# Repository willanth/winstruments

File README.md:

# winstruments
Interface and control PCB for interfacing with professional environmental monitoring instruments

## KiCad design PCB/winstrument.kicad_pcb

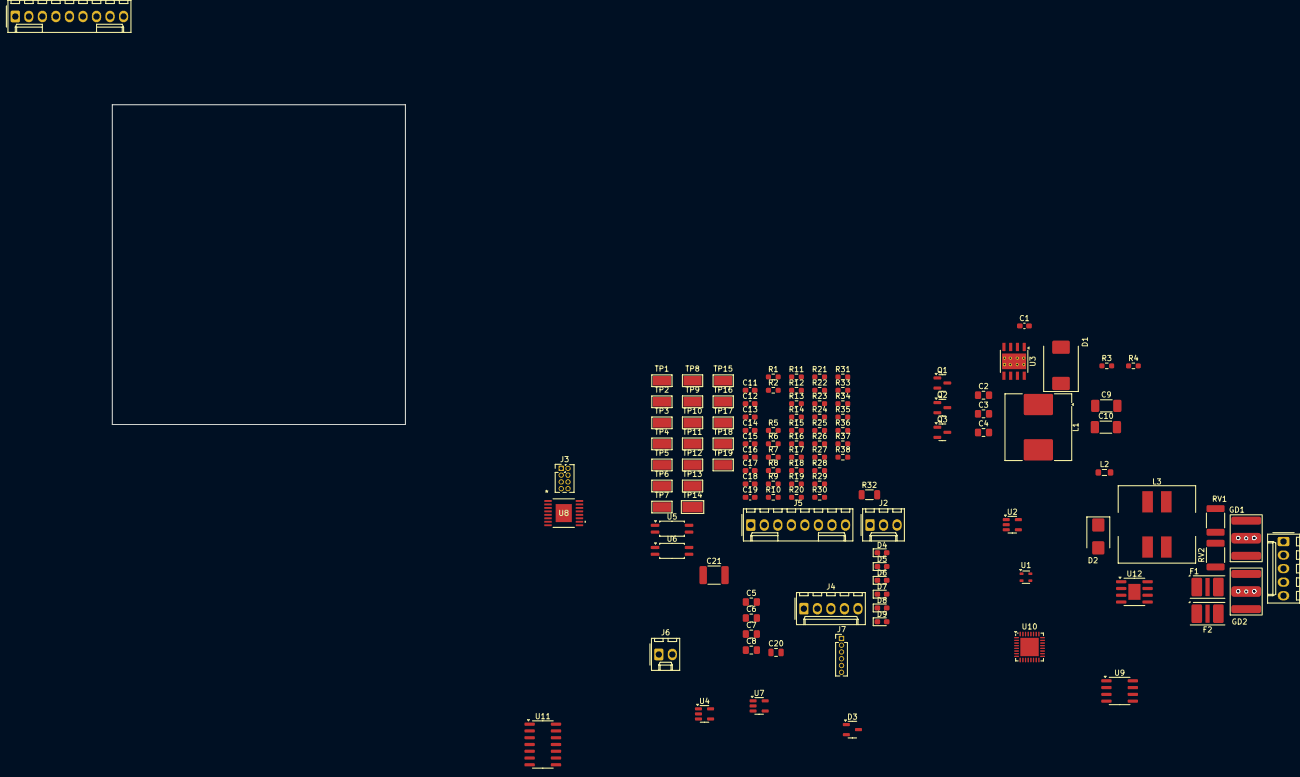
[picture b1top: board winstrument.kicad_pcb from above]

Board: 2 copper layers, 119 parts (0 on the bottom side), 80 nets, no tracks yet.

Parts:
C1: 10nF; C_0603_1608Metric_Pad1.08x0.95mm_HandSolder
C2, C3, C4: 4.7uF 50V; C_0805_2012Metric_Pad1.18x1.45mm_HandSolder
C5, C6, C7, C8: 4.7uF; C_0805_2012Metric_Pad1.18x1.45mm_HandSolder
C9, C10: 27uF 25V; C_1808_4520Metric
C11, C12, C19: 100nF; C_0603_1608Metric_Pad1.08x0.95mm_HandSolder
C13, C14, C15, C16, C17, C18: C; C_0603_1608Metric_Pad1.08x0.95mm_HandSolder
C20: 100nF 50V; C_0805_2012Metric
C21: 100nF 2kV; C_1812_4532Metric
D1: B360; D_SMC
D2: SM6T27A; D_SMB
D3: ESDA5V3L; SOT-23-3
D4, D5, D6, D7, D8, D9: LED; LED_0603_1608Metric_Pad1.05x0.95mm_HandSolder
F1, F2: TBU-CA-025-200-WH; Fuse_Bourns_TBU-CA
GD1, GD2: 3RL075M-5-S; 3R-5-S
J1: Conn_01x05_Pin; Molex_KK-254_AE-6410-05A_1x05_P2.54mm_Vertical
J2: Conn_01x03_Pin; Molex_KK-254_AE-6410-03A_1x03_P2.54mm_Vertical
J3: Conn_02x04_Odd_Even; PinHeader_2x04_P1.27mm_Vertical
J4: RS422; Molex_KK-254_AE-6410-05A_1x05_P2.54mm_Vertical
J5: Conn_01x09_Pin; Molex_KK-254_AE-6410-09A_1x09_P2.54mm_Vertical
J5#2: Conn_01x08_Pin; Molex_KK-254_AE-6410-08A_1x08_P2.54mm_Vertical
J6: Conn_01x02_Pin; Molex_KK-254_AE-6410-02A_1x02_P2.54mm_Vertical
J7: ICSP; PinHeader_1x06_P1.27mm_Vertical
L1: 56uH; L_Coilcraft_MSS1278H-XXX
L2: L_Ferrite; L_0805_2012Metric_Pad1.05x1.20mm_HandSolder
L3: MSD1278-105; MSD1278 SERIES
Q1, Q2, Q3: 2N7002; SOT-23
R1, R2, R3, R23, R26: 10k; R_0603_1608Metric_Pad0.98x0.95mm_HandSolder
R4: 1.13k; R_0603_1608Metric_Pad0.98x0.95mm_HandSolder
R5, R6, R7, R8, R11, R12, R15, R16, R17, R18, R19, R20, R29, R30, R31, R33, R34, R35: R; R_0603_1608Metric_Pad0.98x0.95mm_HandSolder
R9, R10, R13, R14, R21: 1k; R_0603_1608Metric_Pad0.98x0.95mm_HandSolder
R22, R24, R25, R27, R28: 3.3k; R_0603_1608Metric_Pad0.98x0.95mm_HandSolder
R32: 1M; R_1206_3216Metric
R36, R37, R38: 100k; R_0603_1608Metric_Pad0.98x0.95mm_HandSolder
RV1, RV2: Varistor; R_1812_4532Metric_Pad1.30x3.40mm_HandSolder
TP1, TP2, TP3, TP4, TP5, TP6, TP7, TP8, TP9, TP11, TP12, TP13, TP15, TP16, TP17, TP18, TP19: TestPoint_Alt; TestPoint_Keystone_5015_Micro-Minature
TP10: TestPoint; TestPoint_Keystone_5015_Micro-Minature
TP14: TestPoint_Alt; TestPoint_Keystone_5019_Minature
U1: NCP662SQ50; SC-82AB
U2: TLV75533PDBV; SOT-23-5
U3: TPS5430DDA; TI_SO-PowerPAD-8_ThermalVias
U4, U7: TLV9061xDBV; SOT-23-5
U5, U6: TCMT1100; SOP-4_4.4x2.6mm_P1.27mm
U8: TPS27SA08CPWPR; TSSOP_CPWPR_TEX
U9: ADM3488ExR; SOIC-8_3.9x4.9mm_P1.27mm
U10: STM32L432KCUx; QFN-32-1EP_5x5mm_P0.5mm_EP3.45x3.45mm
U11: TXB0104D; SOIC-14_3.9x8.7mm_P1.27mm
U12: TCAN337; SOIC-8-1EP_3.9x4.9mm_P1.27mm_EP2.29x3mm

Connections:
+3V3: C8.1, C11.1, C12.1, C13.2, C14.2, C15.1, C16.1, C17.1, C19.2, D9.2 (A), R9.1, R10.1, R13.1, R14.1, R23.1, R26.2, TP2.1, U2.5 (OUT), U4.5 (V+), U7.5 (V+), U9.1 (VCC), U10.1 (VDD), U10.5 (VDDA), U10.17 (VDD), U11.1 (VCCA), U12.3 (VCC)
+5V: C6.1, D4.2 (A), D5.2 (A), D6.2 (A), D8.2 (A), J3.6, TP1.1, U1.3 (VOUT), U11.14 (VCCB)
+12V: C5.1, C7.1, C9.1, C10.1, D7.2 (A), J3.4, L1.2, R1.1, R2.1, R3.2, TP3.1, U1.2 (VIN), U2.1 (IN)
+24V: C2.1, C3.1, C4.1, J3.2, L2.1, U3.7 (VIN)
+VDC: GD1.3, J1.1, L3.2, RV1.1, TP4.1
/ADC_1: R5.2, R12.1, TP6.1, U4.1, U10.7 (PA1)
/ADC_2: R15.2, R20.1, TP9.1, U7.1, U10.9 (PA3)
/AMP1+: J5.1, J5#2.1, R6.1
/AMP1-: J5.2, J5#2.2, R8.1
/AMP2+: J5.3, J5#2.3, R16.1
/AMP2-: J5.4, J5#2.4, R18.1
/CAN_FAULT: TP17.1, U10.13 (PA7), U12.5 (FAULT)
/CAN_H: D3.2 (K), F1.1, TP15.1, U12.7 (CANH)
/CAN_L: D3.1 (K), F2.1, TP18.1, U12.6 (CANL)
/CAN_RX: U10.21 (PA11), U12.4 (RXD)
/CAN_S: TP19.1, U12.8 (S)
/CAN_TX: U10.22 (PA12), U12.1 (TXD)
/COUNTER: TP13.1, U10.18 (PA8)
/DIA_EN: R22.1, TP16.1, U10.29 (PB6)
/GPIO_1: U10.6 (PA0), U11.2 (A1)
/GPIO_2: U10.8 (PA2), U11.3 (A2)
/GPIO_3: U10.10 (PA4), U11.4 (A3)
/GPIO_4: U10.11 (PA5), U11.5 (A4)
/NRST: C18.2, J7.5, R23.2, U10.4 (NRST)
/POUT_EN: R24.2, TP14.1, U10.25 (PA15), U10.27 (PB4)
/SEL1: R27.1, U10.2 (PC14)
/SEL2: R25.1, U10.3 (PC15)
/SENSE: R21.1, U8.2 (SNS)
/SERIAL_DEV_RX: J2.2, R13.2, U6.4
/SERIAL_DEV_TX: J2.1, R9.2, U5.1
/SHIFT_OE: U10.12 (PA6), U11.8 (OE)
/STAT_1: Q1.1 (G), R36.1, U10.15 (PB1)
/STAT_2: Q2.1 (G), R37.1, U10.14 (PB0)
/STAT_3: Q3.1 (G), R38.1
/SWCLK: J7.2, U10.24 (PA14)
/SWDIO: J7.4, U10.23 (PA13)
/SWO: J7.6, U10.26 (PB3)
/UART_RX: R10.2, TP11.1, U5.4, U9.2 (RO), U10.20 (PA10)
/UART_TX: R14.2, TP12.1, U6.1, U9.3 (DI), U10.19 (PA9)
/V_LOAD: C20.2, J6.1, U8.6 (VOUT), U8.7 (VOUT), U8.8 (VOUT), U8.10 (VOUT), U8.11 (VOUT)
/~ST: R28.2, U10.28 (PB5)
Earth: C21.2, D3.3 (A), GD1.2, GD2.2, J1.5, J2.3, J4.5, J5.9, R32.2, RV1.2, RV2.2
GND: C2.2, C3.2, C4.2, C5.2, C6.2, C7.2, C8.2, C9.2, C10.2, C11.2, C12.2, C13.1, C14.1, C15.2, C16.2, C17.2, C18.1, C19.1, C20.1, C21.1, D1.2 (A), D2.2 (A2), J6.2, J7.3, L3.3, Q1.2 (S), Q2.2 (S), Q3.2 (S), R4.2, R7.2, R11.2, R17.2, R19.2, R21.2, R32.1, R33.2, R34.2, R35.2, R36.2, R37.2, R38.2, TP7.1, U1.1 (GND), U2.2 (GND), U3.6 (GND), U3.9 (GNDPAD), U4.2 (V-), U5.2, U5.3, U6.2, U6.3, U7.2 (V-), U8.1 (GND), U9.4 (GND), U10.16 (VSS), U10.32 (VSS), U10.33 (VSS), U11.7 (GND), U12.2 (GND)
GNDPWR: GD1.1, J1.2, L3.4, RV2.1, TP8.1
unnamed: C1.2, D1.1 (K), L1.1, U3.8 (PH)
unnamed: D2.1 (A1), L2.2, L3.1, TP5.1
unnamed: D4.1 (K), R29.1
unnamed: D5.1 (K), R30.1
unnamed: D6.1 (K), R31.1
unnamed: D7.1 (K), R33.1
unnamed: D8.1 (K), R34.1
unnamed: D9.1 (K), R35.1
unnamed: F1.3, GD2.3, J1.3
unnamed: F2.3, GD2.1, J1.4
unnamed: J3.1, J3.3, J3.5, J3.7, U8.EPAD (VBB)
unnamed: J3.8, TP10.1
unnamed: J4.1, U9.8 (A)
unnamed: J4.2, U9.7 (B)
unnamed: J4.3, U9.6 (Z)
unnamed: J4.4, U9.5 (Y)
unnamed: J5.5, J5#2.5, U11.13 (B1)
unnamed: J5.6, J5#2.6, U11.12 (B2)
unnamed: J5.7, J5#2.7, U11.11 (B3)
unnamed: J5.8, J5#2.8, U11.10 (B4)
unnamed: Q1.3 (D), R29.2
unnamed: Q2.3 (D), R30.2
unnamed: Q3.3 (D), R31.2
unnamed: R2.2, U1.4 (EN)
unnamed: R1.2, U2.3 (EN)
unnamed: C1.1, U3.1 (BOOT)
unnamed: R3.1, R4.1, U3.4 (VSENSE)
unnamed: R5.1, R6.2, R7.1, U4.3 (+)
unnamed: R8.2, R11.1, R12.2, U4.4 (-)
unnamed: R15.1, R16.2, R17.1, U7.3 (+)
unnamed: R18.2, R19.1, R20.2, U7.4 (-)
unnamed: R22.2, U8.16 (DIA_EN)
unnamed: R24.1, U8.4 (EN)
unnamed: R27.2, U8.14 (SEL1)
unnamed: R25.2, U8.15 (SEL2)
unnamed: R26.1, R28.1, U8.5 (ST)

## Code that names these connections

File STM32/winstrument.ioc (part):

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Mcu.Name=STM32L432K(B-C)Ux
Mcu.Package=UFQFPN32
Mcu.UserName=STM32L432KCUx
PA0.GPIOParameters=GPIO_Label
PA0.GPIO_Label=MCO [High speed clock in]
PA0.Mode=HSE-External-Clock-Source-for-LittleOrca
PA0.Signal=RCC_CK_IN
PA1.Signal=ADCx_IN6
PA10.Mode=Asynchronous
PA10.Signal=USART1_RX
PA11.Mode=CAN_Activate
PA11.Signal=CAN1_RX
PA12.Mode=CAN_Activate
PA12.Signal=CAN1_TX
PA13\ (JTMS-SWDIO).GPIOParameters=GPIO_Label
PA13\ (JTMS-SWDIO).GPIO_Label=SWDIO
PA13\ (JTMS-SWDIO).Mode=Serial_Wire
PA13\ (JTMS-SWDIO).Signal=SYS_JTMS-SWDIO
PA14\ (JTCK-SWCLK).GPIOParameters=GPIO_Label
PA14\ (JTCK-SWCLK).GPIO_Label=SWCLK
PA14\ (JTCK-SWCLK).Mode=Serial_Wire
PA14\ (JTCK-SWCLK).Signal=SYS_JTCK-SWCLK
PA15\ (JTDI).GPIOParameters=GPIO_Label
PA15\ (JTDI).GPIO_Label=VCP_RX
PA15\ (JTDI).Mode=Asynchronous
PA15\ (JTDI).Signal=USART2_RX
PA2.GPIOParameters=GPIO_Label
PA2.GPIO_Label=VCP_TX
PA2.Mode=Asynchronous
PA2.Signal=USART2_TX
PA3.Signal=ADCx_IN8
PA6.GPIOParameters=GPIO_Label
PA6.GPIO_Label=SH
PA6.Signal=GPIO_Output
PA7.GPIOParameters=GPIO_Label
PA7.GPIO_Label=STAT_3
PA7.Signal=GPIO_Output
PA8.Signal=S_TIM1_CH1
PA9.Mode=Asynchronous
PA9.Signal=USART1_TX
PB0.GPIOParameters=GPIO_Label
PB0.GPIO_Label=STAT_2
PB0.Signal=GPIO_Output
PB1.GPIOParameters=GPIO_Label
PB1.GPIO_Label=STAT_1
PB1.Signal=GPIO_Output
PC14-OSC32_IN\ (PC14).Mode=LSE-External-Oscillator
PC14-OSC32_IN\ (PC14).Signal=RCC_OSC32_IN
PC15-OSC32_OUT\ (PC15).Mode=LSE-External-Oscillator
PC15-OSC32_OUT\ (PC15).Signal=RCC_OSC32_OUT
RCC.HSE_VALUE=8000000
RCC.SYSCLKFreq_VALUE=32000000
RCC.SYSCLKSource=RCC_SYSCLKSOURCE_PLLCLK
board=NUCLEO-L432KC
boardIOC=true

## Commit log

2024-06-29 initial commit from local files and work
2024-06-29 initial commit of an STM32 Cube IDE project used to develop basic functionality
2024-07-11 beginning STM32 project configuration
2024-07-11 begin PCB schemaitic layout for a universal instrument interface
2025-01-17 modification of the knowledgebase to fold in other work that had been accidentally duplicated. Small progress on the schematic, evaluating using a digital isolator instead of an optoisolator for offb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
2025-02-03 schematic capture and part specification mostly complete. Still some uncertainty on the power common mode filter choke, could possibly go with a through-hole part on a toroid. At least one footprint 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
2025-05-14 commit to catch up the repo to changes in PCB design
2025-06-26 modified schematics to replace parts and redesign serial interfaces. Replaced general purpose opamps with adjustable gain instrumentation amplifiers that are more appropriate.
2025-06-30 replaced microcontroller due to requirements for more interface pins and additional capabilities in processing power and memory that would improve performance in signal processing
2025-11-05 committing leftovers from the past, prior to modifying PCBs for optoisolators
